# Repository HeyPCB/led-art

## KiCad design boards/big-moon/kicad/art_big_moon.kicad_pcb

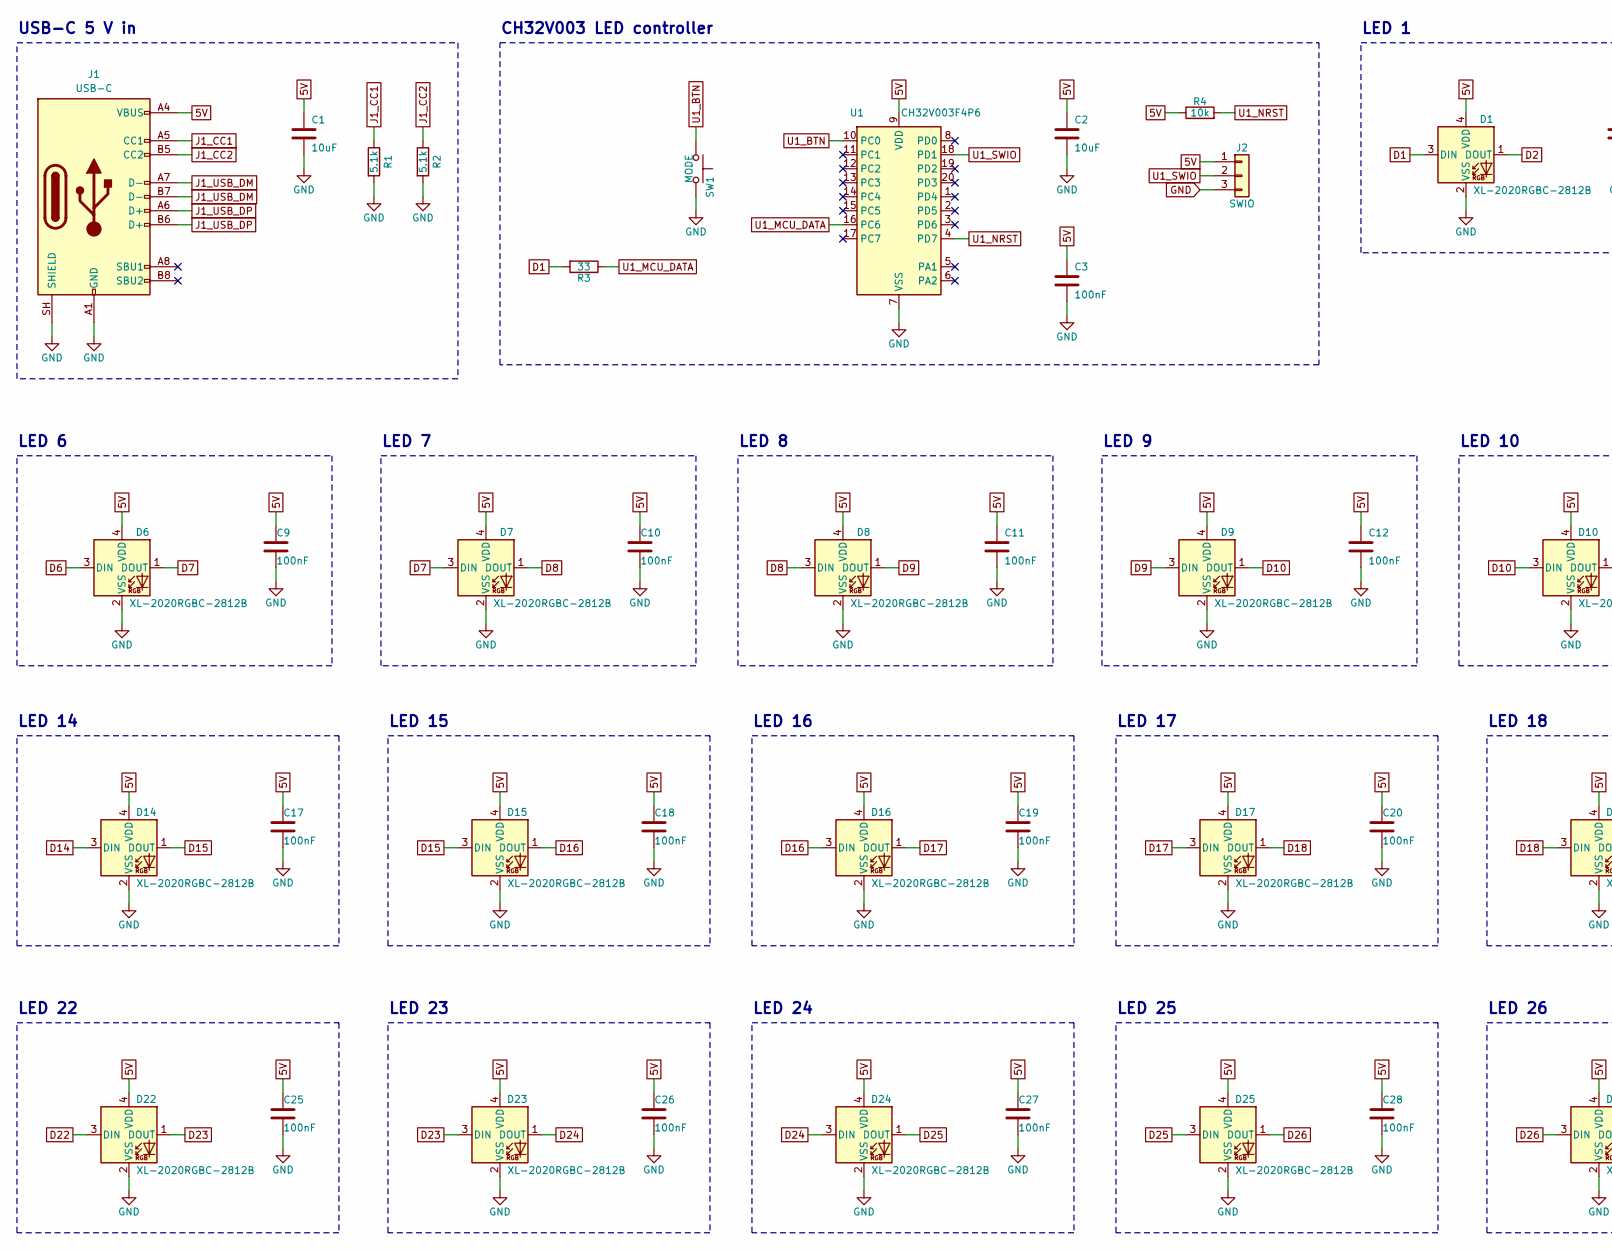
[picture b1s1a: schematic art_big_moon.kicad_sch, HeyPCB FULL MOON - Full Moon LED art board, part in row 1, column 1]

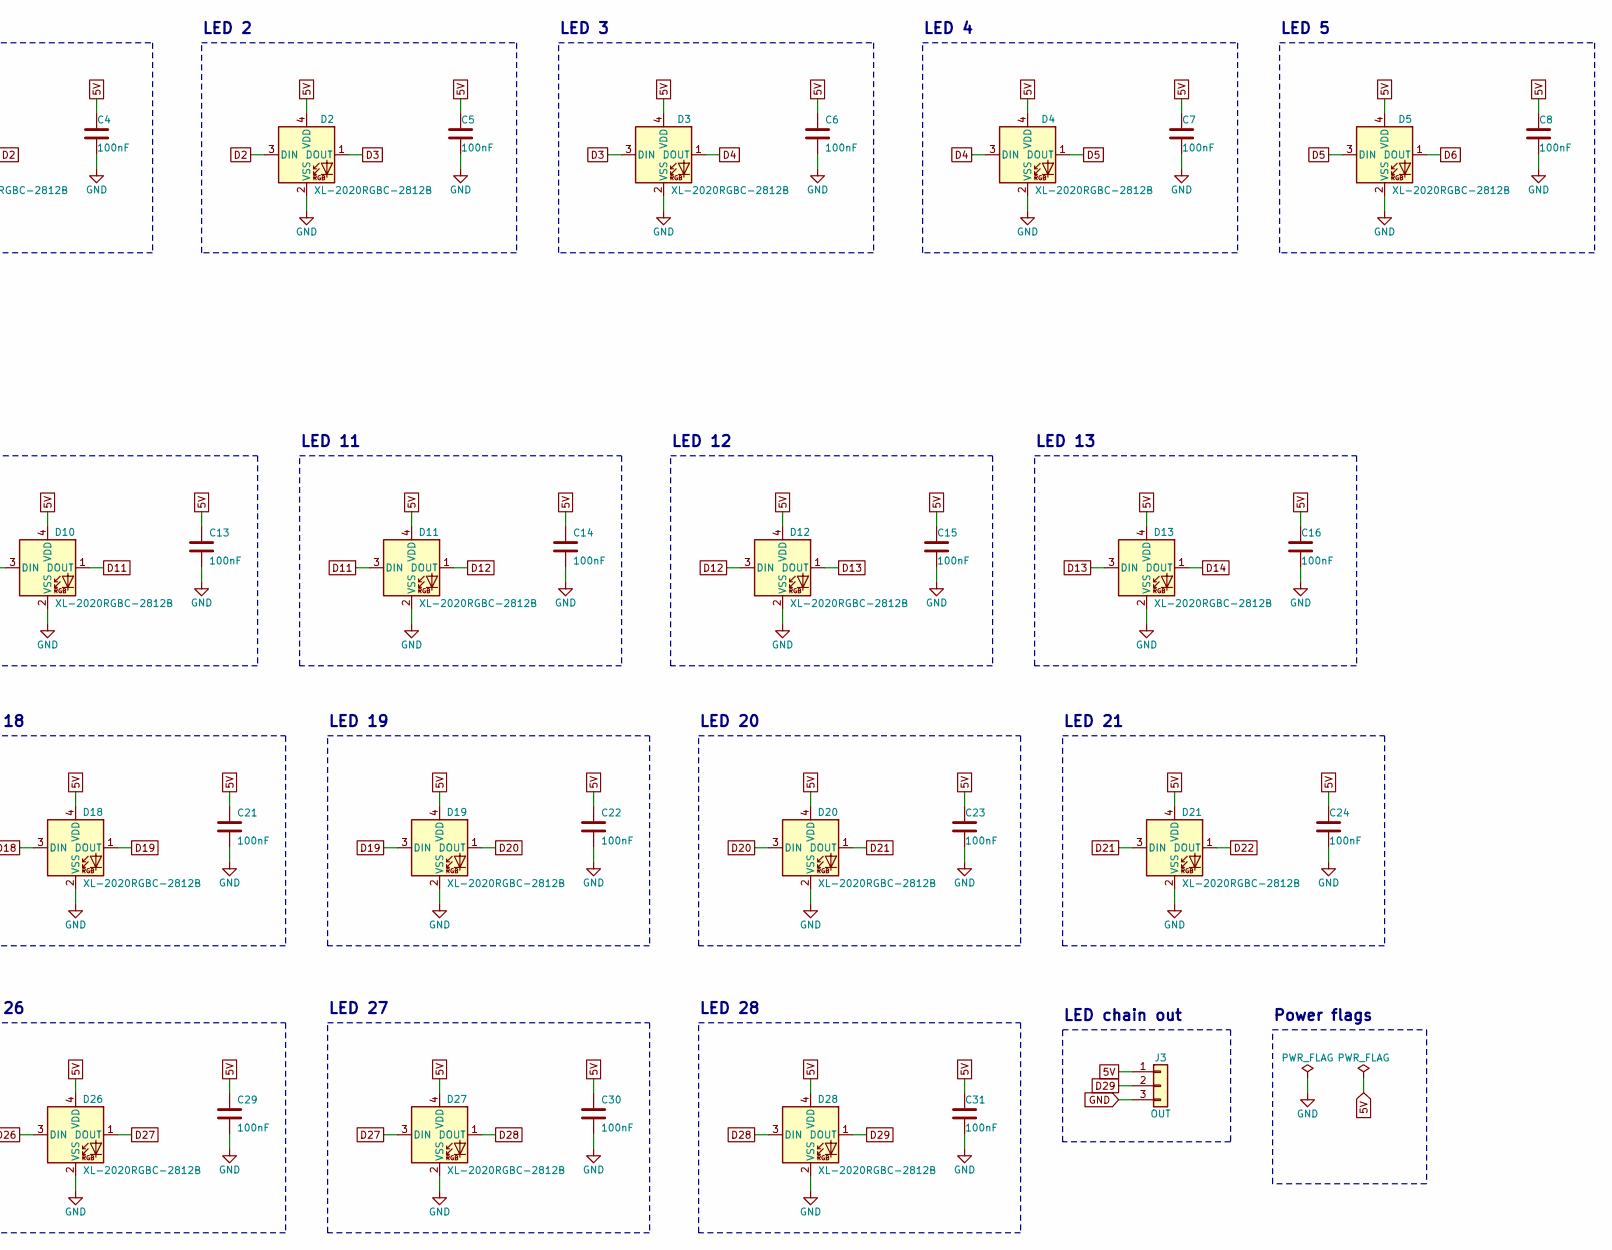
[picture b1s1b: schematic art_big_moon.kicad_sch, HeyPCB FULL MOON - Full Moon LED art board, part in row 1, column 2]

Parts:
C1, C2: 10uF; C_0805_2012Metric; MPN CL21A106KAYNNNE; LCSC C15850
C3, C4, C5, C6, C7, C8, C9, C10, C11, C12, C13, C14, C15, C16, C17, C18, C19, C20, C21, C22, C23, C24, C25, C26, C27, C28, C29, C30, C31: 100nF; C_0402_1005Metric; MPN CL05B104KO5NNNC; LCSC C1525
D1, D2, D3, D4, D5, D6, D7, D8, D9, D10, D11, D12, D13, D14, D15, D16, D17, D18, D19, D20, D21, D22, D23, D24, D25, D26, D27, D28: XL-2020RGBC-2812B; LED_WS2812B-2020_PLCC4_2.0x2.0mm; MPN XL-2020RGBC-2812B; LCSC C5349955
J1: USB-C; USB_C_Receptacle_HRO_TYPE-C-31-M-12; MPN TYPE-C-31-M-12; LCSC C165948
J2: SWIO; PinHeader_1x03_P2.54mm_Vertical; MPN PZ254V-11-03P; LCSC C2937625
J3: OUT; PinHeader_1x03_P2.54mm_Vertical; MPN PZ254V-11-03P; LCSC C2937625
R1, R2: 5.1k; R_0402_1005Metric; MPN 0402WGF5101TCE; LCSC C25905
R3: 33; R_0603_1608Metric; MPN 0603WAF330JT5E; LCSC C23140
R4: 10k; R_0603_1608Metric; MPN 0603WAF1002T5E; LCSC C25804
SW1: MODE; SW_Push_1P1T_XKB_TS-1187A; MPN TS-1187A-B-A-B; LCSC C318884
U1: CH32V003F4P6; TSSOP-20_4.4x6.5mm_P0.65mm; MPN CH32V003F4P6; LCSC C5187096

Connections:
5V: C1.1, C2.1, C3.1, C4.1, C5.1, C6.1, C7.1, C8.1, C9.1, C10.1, C11.1, C12.1, C13.1, C14.1, C15.1, C16.1, C17.1, C18.1, C19.1, C20.1, C21.1, C22.1, C23.1, C24.1, C25.1, C26.1, C27.1, C28.1, C29.1, C30.1, C31.1, D1.4 (VDD), D2.4 (VDD), D3.4 (VDD), D4.4 (VDD), D5.4 (VDD), D6.4 (VDD), D7.4 (VDD), D8.4 (VDD), D9.4 (VDD), D10.4 (VDD), D11.4 (VDD), D12.4 (VDD), D13.4 (VDD), D14.4 (VDD), D15.4 (VDD), D16.4 (VDD), D17.4 (VDD), D18.4 (VDD), D19.4 (VDD), D20.4 (VDD), D21.4 (VDD), D22.4 (VDD), D23.4 (VDD), D24.4 (VDD), D25.4 (VDD), D26.4 (VDD), D27.4 (VDD), D28.4 (VDD), J1.A4 (VBUS), J1.A9 (VBUS), J1.B4 (VBUS), J1.B9 (VBUS), J2.1, J3.1, R4.1, U1.9 (VDD)
D1: D1.3 (DIN), R3.2
D2: D1.1 (DOUT), D2.3 (DIN)
D3: D2.1 (DOUT), D3.3 (DIN)
D4: D3.1 (DOUT), D4.3 (DIN)
D5: D4.1 (DOUT), D5.3 (DIN)
D6: D5.1 (DOUT), D6.3 (DIN)
D7: D6.1 (DOUT), D7.3 (DIN)
D8: D7.1 (DOUT), D8.3 (DIN)
D9: D8.1 (DOUT), D9.3 (DIN)
D10: D9.1 (DOUT), D10.3 (DIN)
D11: D10.1 (DOUT), D11.3 (DIN)
D12: D11.1 (DOUT), D12.3 (DIN)
D13: D12.1 (DOUT), D13.3 (DIN)
D14: D13.1 (DOUT), D14.3 (DIN)
D15: D14.1 (DOUT), D15.3 (DIN)
D16: D15.1 (DOUT), D16.3 (DIN)
D17: D16.1 (DOUT), D17.3 (DIN)
D18: D17.1 (DOUT), D18.3 (DIN)
D19: D18.1 (DOUT), D19.3 (DIN)
D20: D19.1 (DOUT), D20.3 (DIN)
D21: D20.1 (DOUT), D21.3 (DIN)
D22: D21.1 (DOUT), D22.3 (DIN)
D23: D22.1 (DOUT), D23.3 (DIN)
D24: D23.1 (DOUT), D24.3 (DIN)
D25: D24.1 (DOUT), D25.3 (DIN)
D26: D25.1 (DOUT), D26.3 (DIN)
D27: D26.1 (DOUT), D27.3 (DIN)
D28: D27.1 (DOUT), D28.3 (DIN)
D29: D28.1 (DOUT), J3.2
GND: C1.2, C2.2, C3.2, C4.2, C5.2, C6.2, C7.2, C8.2, C9.2, C10.2, C11.2, C12.2, C13.2, C14.2, C15.2, C16.2, C17.2, C18.2, C19.2, C20.2, C21.2, C22.2, C23.2, C24.2, C25.2, C26.2, C27.2, C28.2, C29.2, C30.2, C31.2, D1.2 (VSS), D2.2 (VSS), D3.2 (VSS), D4.2 (VSS), D5.2 (VSS), D6.2 (VSS), D7.2 (VSS), D8.2 (VSS), D9.2 (VSS), D10.2 (VSS), D11.2 (VSS), D12.2 (VSS), D13.2 (VSS), D14.2 (VSS), D15.2 (VSS), D16.2 (VSS), D17.2 (VSS), D18.2 (VSS), D19.2 (VSS), D20.2 (VSS), D21.2 (VSS), D22.2 (VSS), D23.2 (VSS), D24.2 (VSS), D25.2 (VSS), D26.2 (VSS), D27.2 (VSS), D28.2 (VSS), J1.A1 (GND), J1.A12 (GND), J1.B1 (GND), J1.B12 (GND), J1.SH (SHIELD), J2.3, J3.3, R1.2, R2.2, SW1.2, U1.7 (VSS)
J1_CC1: J1.A5 (CC1), R1.1
J1_CC2: J1.B5 (CC2), R2.1
J1_USB_DM: J1.A7 (D-), J1.B7 (D-)
J1_USB_DP: J1.A6 (D+), J1.B6 (D+)
U1_BTN: SW1.1, U1.10 (PC0)
U1_MCU_DATA: R3.1, U1.16 (PC6)
U1_NRST: R4.2, U1.4 (PD7)
U1_SWIO: J2.2, U1.18 (PD1)

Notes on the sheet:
USB-C 5 V in
CH32V003 LED controller
LED 1
LED 2
LED 3
LED 4
LED 5
LED 6
LED 7
LED 8
LED 9
LED 10
LED 11
LED 12
LED 13
LED 14
LED 15
LED 16
LED 17
LED 18
LED 19
LED 20
LED 21
LED 22
LED 23
LED 24
LED 25
LED 26
LED 27
LED 28
LED chain out
Power flags

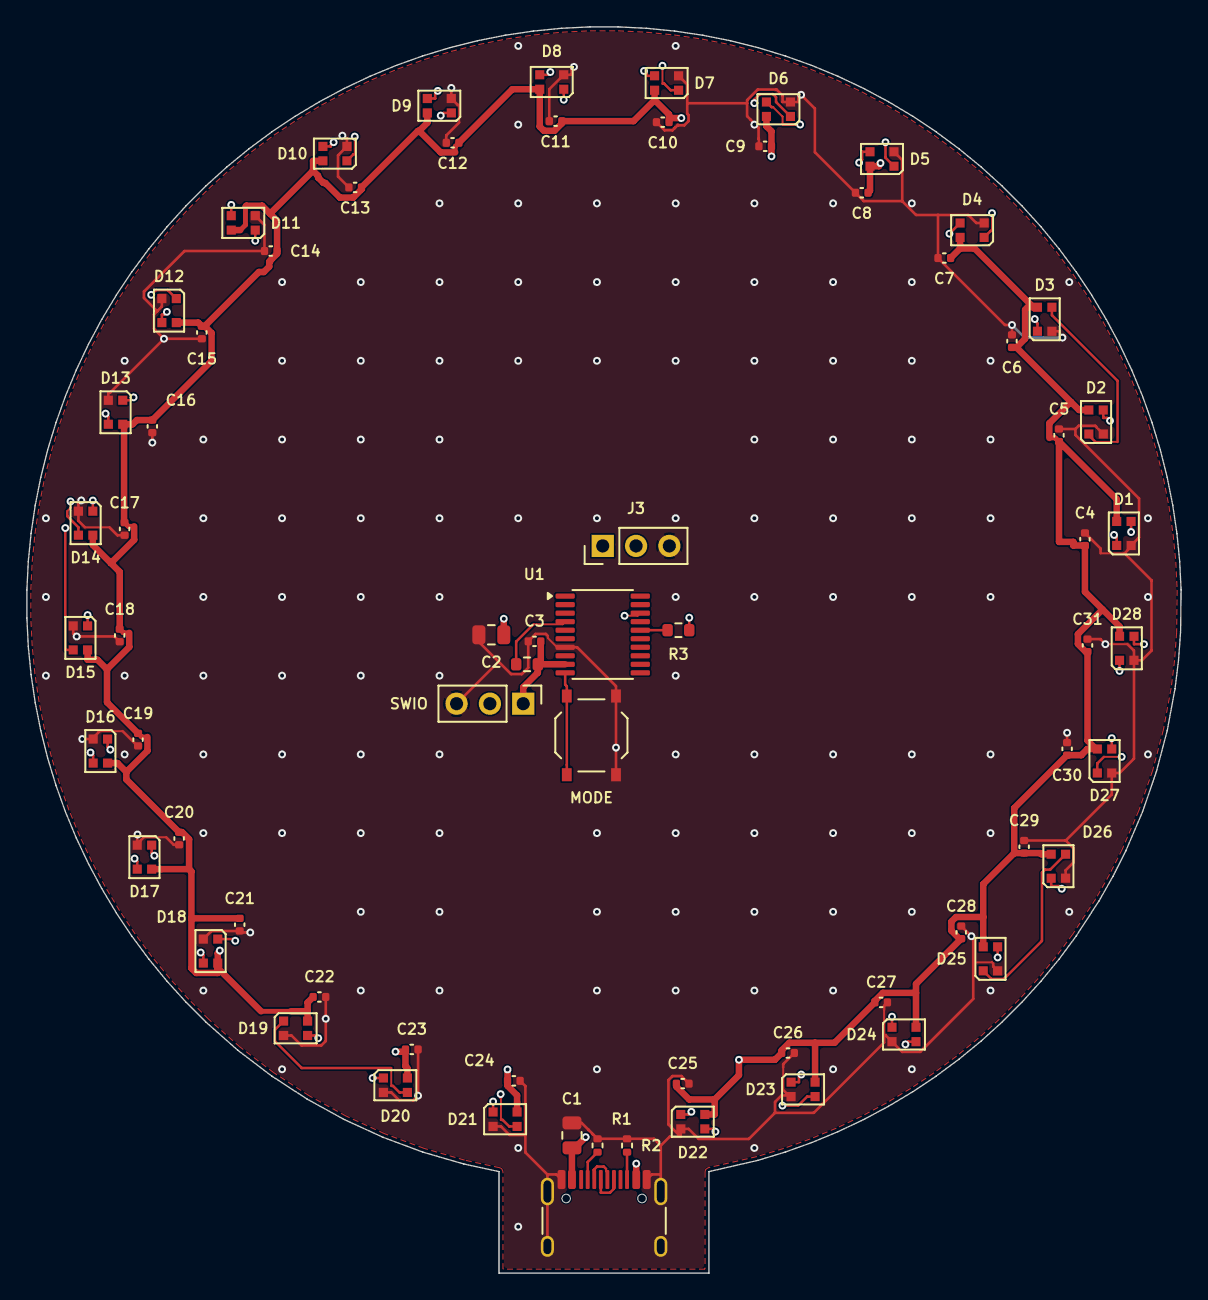
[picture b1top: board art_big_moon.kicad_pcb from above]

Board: 4 copper layers, 88.0 x 95.0 mm, 68 parts (0 on the bottom side), 39 nets.

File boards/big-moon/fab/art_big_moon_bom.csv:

"Reference","Value","Footprint","MPN","LCSC","Qty"
"C1,C2","10uF","Capacitor_SMD:C_0805_2012Metric","CL21A106KAYNNNE","C15850","2"
"C3,C4,C5,C6,C7,C8,C9,C10,C11,C12,C13,C14,C15,C16,C17,C18,C19,C20,C21,C22,C23,C24,C25,C26,C27,C28,C29,C30,C31","100nF","Capacitor_SMD:C_0402_1005Metric","CL05B104KO5NNNC","C1525","29"
"D1,D2,D3,D4,D5,D6,D7,D8,D9,D10,D11,D12,D13,D14,D15,D16,D17,D18,D19,D20,D21,D22,D23,D24,D25,D26,D27,D28","XL-2020RGBC-2812B","LED_SMD:LED_WS2812B-2020_PLCC4_2.0x2.0mm","XL-2020RGBC-2812B","C5349955","28"
"J1","USB-C","Connector_USB:USB_C_Receptacle_HRO_TYPE-C-31-M-12","TYPE-C-31-M-12","C165948","1"
"J2","SWIO","Connector_PinHeader_2.54mm:PinHeader_1x03_P2.54mm_Vertical","PZ254V-11-03P","C2937625","1"
"J3","OUT","Connector_PinHeader_2.54mm:PinHeader_1x03_P2.54mm_Vertical","PZ254V-11-03P","C2937625","1"
"R1,R2","5.1k","Resistor_SMD:R_0402_1005Metric","0402WGF5101TCE","C25905","2"
"R3","33","Resistor_SMD:R_0603_1608Metric","0603WAF330JT5E","C23140","1"
"R4","10k","Resistor_SMD:R_0603_1608Metric","0603WAF1002T5E","C25804","1"
"SW1","MODE","Button_Switch_SMD:SW_Push_1P1T_XKB_TS-1187A","TS-1187A-B-A-B","C318884","1"
"U1","CH32V003F4P6","Package_SO:TSSOP-20_4.4x6.5mm_P0.65mm","CH32V003F4P6","C5187096","1"
